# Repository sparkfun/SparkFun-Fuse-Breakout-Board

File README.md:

SparkFun Fuse Breakout Board
========================================

<table class="table table-hover table-striped table-bordered">
  <tr align="center">
   <td></td>
   <td></td>
  </tr>
  <tr align="center">
   <td><i>SparkFun Fuse Breakout Board [<a href="https://www.sparkfun.com/products/15697">BOB-15697</a>]</i></td>
   <td><i>SparkFun Fuse Breakout Kit [<a href="https://www.sparkfun.com/products/15702">KIT-15702</a>]</i></td>
  </tr>
</table>

This is a breakout board for the glass ferrule type fuse. It fits great with our [5mm fuse clips](https://www.sparkfun.com/products/9773). Fuses are pretty simple, if current exceeds the rating of the fuse, the small filament inside the fuse heats up and breaks (like a light bulb burning out). The circuit is then broken and hopefully your circuit is saved from molten destruction.

For smaller loads, you may want to checkout a PTC (aka resettable fuse). They handle less current (500mA) but can be set and reset many times without doing harm to your system.

_Note: The PCB was designed for DC power. It was not designed for AC power. Make sure that you are using the fuse breakout on the DC side for protection!_

Repository Contents
-------------------

* **/Documentation** - Data sheets, additional product information
* **/Hardware** - Eagle design files (.brd, .sch)

Repository Contents
-------------------

* **[Hookup Guide](https://learn.sparkfun.com/tutorials/fuse-breakout-board-hookup-guide)** - Basic hookup guide
* **[SparkFun Fritzing repo](https://github.com/sparkfun/Fritzing_Parts)** - Fritzing diagrams for SparkFun products.

Product Versions
----------------
* [BOB-15697](https://www.sparkfun.com/products/15697) - Breakout board, V1
* [KIT-15702](https://www.sparkfun.com/products/15702) - Kit version with breakout, glass fuse, connectors, and clips

License Information
-------------------

This product is _**open source**_! 

Please review the LICENSE.md file for license information. 

If you have any questions or concerns on licensing, please contact technical support on our [SparkFun forums](https://forum.sparkfun.com/viewforum.php?f=152).

Distributed as-is; no warranty is given.

- Your friends at SparkFun.

_<COLLABORATION CREDIT>_

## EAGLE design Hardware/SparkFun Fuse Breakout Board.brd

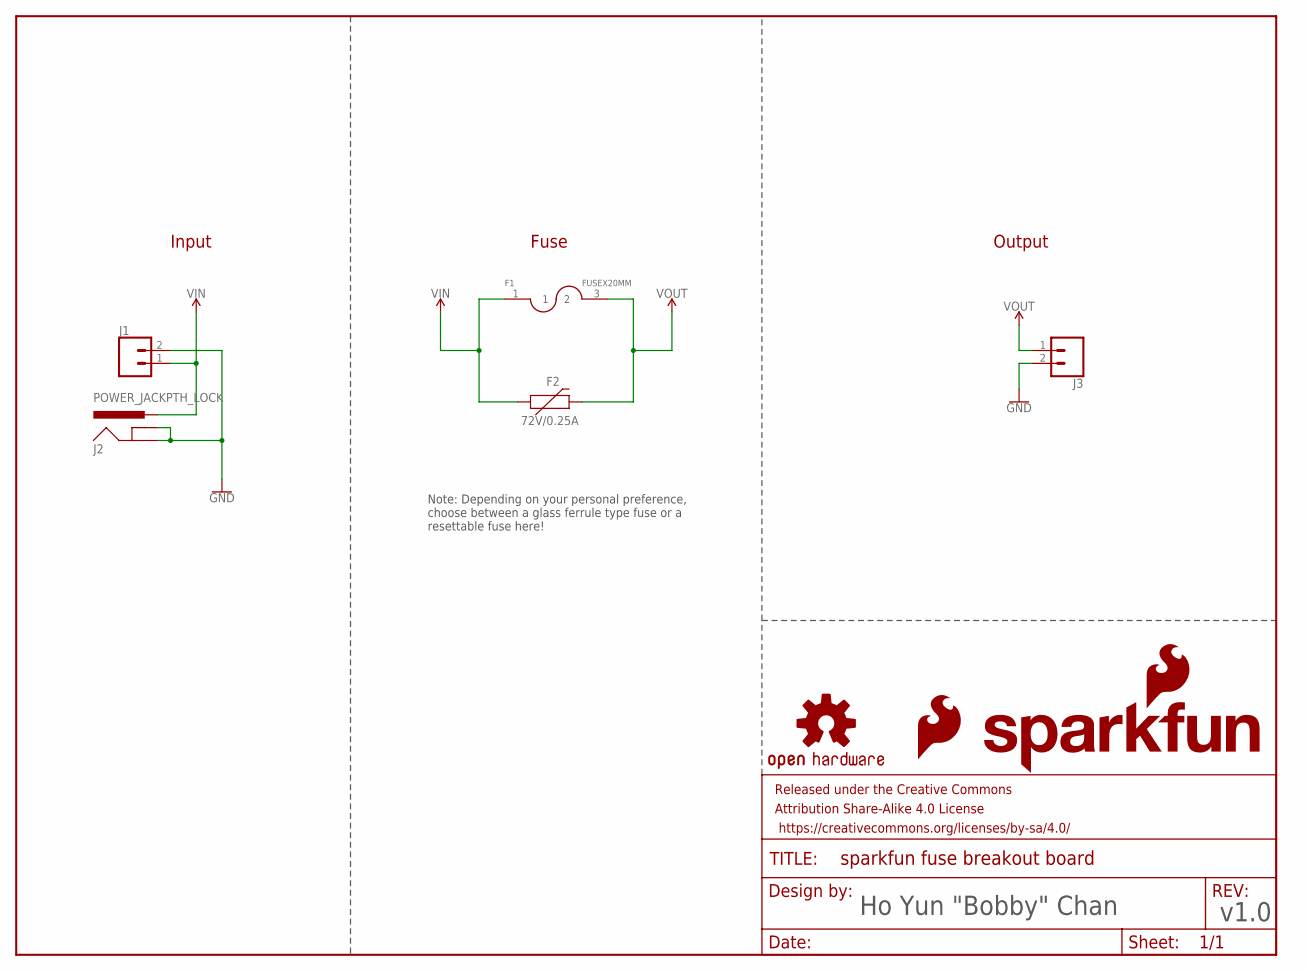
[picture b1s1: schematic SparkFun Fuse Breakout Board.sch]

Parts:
F1: FUSEX20MM; FUSE_5MM
F2: 72V/0.25A; PTH
FRAME1: FRAME-LETTER; CREATIVE_COMMONS
J1, J3: CONN_025MM; SCREWTERMINAL-5MM-2
J2: POWER_JACKPTH_LOCK; POWER_JACK_PTH_LOCK
LOGO1: SFE_LOGO_NAME_FLAME.1_INCH; SFE_LOGO_NAME_FLAME_.1
LOGO2: SFE_LOGO_FLAME.1_INCH; SFE_LOGO_FLAME_.1
LOGO3: OSHW-LOGOMINI; OSHW-LOGO-MINI

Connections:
GND: J1.2, J2.GND, J2.GNDBREAK, J3.2
VIN: F1.1, F2.P$1 (1), J1.1, J2.PWR
VOUT: F1.3 (2), F2.P$2 (2), J3.1

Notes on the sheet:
Fuse
Output
Input
Ho Yun "Bobby" Chan
v1.0
Note: Depending on your personal preference, choose between a glass ferrule type fuse or a resettable fuse here!

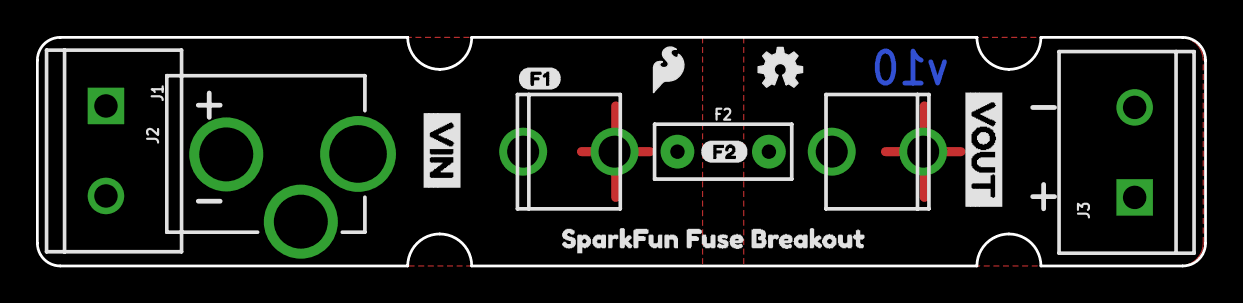
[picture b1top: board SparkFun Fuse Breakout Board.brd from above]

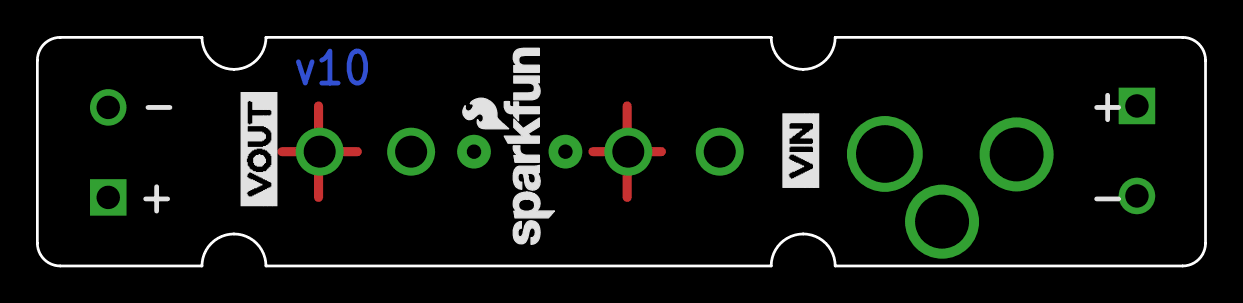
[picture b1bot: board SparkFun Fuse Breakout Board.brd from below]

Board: 2 copper layers, 64.9 x 12.7 mm, 16 parts (3 on the bottom side), 3 nets.

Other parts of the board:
U$1, U$4: VIN0
U$2, U$3: VOUT0
U$11: SPARKFUN_FUSE_BREAKOUT0
U$28: F10
U$29: F20

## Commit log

2019-06-14 Eagle Files and git files
2019-08-02 Update board
    - rotate version number
    - split top polygon layer to VIN and VOUT
    - add t-stop isolate with screw terminals
    - remove SMD Fuse
    - remove 0.1" PTH pins
    - use screw terminal instead of PTH pins
2019-08-02 Update Board
    - move silkscreen for screw terminals
    - remove stand offs and add top/bottom restrict for half mounting holes
    - adjust isolation for polygon pours
    - adjust polygon pour width for VIN and VOUT by F2
    - big buzzard labels for VIN and VOUT
2019-08-02 Update SparkFun Fuse Breakout Board.brd
    - rotate label on back to match SFE logo
2019-08-23 Update SparkFun Fuse Breakout Board.brd
    - Move +/- silkscreen on back closer to screw terminals to be consistent with VIN and VOUT sides
2019-09-27 Create SparkFun_Fuse_Breakout_Board_Dimensions.png
    - Board Dimensions
2019-09-27 Update Note in Schematic

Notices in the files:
parts and their libraries:
SparkFun-Fuses: Licensing: Creative Commons ShareAlike 4.0 International - https://creativecommons.org/licenses/by-sa/4.0
SparkFun-Aesthetics: Released under the Creative Commons Attribution Share-Alike 4.0 License
SparkFun-Aesthetics: https://creativecommons.org/licenses/by-sa/4.0
